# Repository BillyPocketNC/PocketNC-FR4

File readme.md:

# Support for this Project has been discontinued
This is an open source project and is not commercially supported.

For more information and files see [our Wiki](https://pocketnc.atlassian.net/wiki/spaces/PNFUR/pages/368902363/FR4+Resources) for more information

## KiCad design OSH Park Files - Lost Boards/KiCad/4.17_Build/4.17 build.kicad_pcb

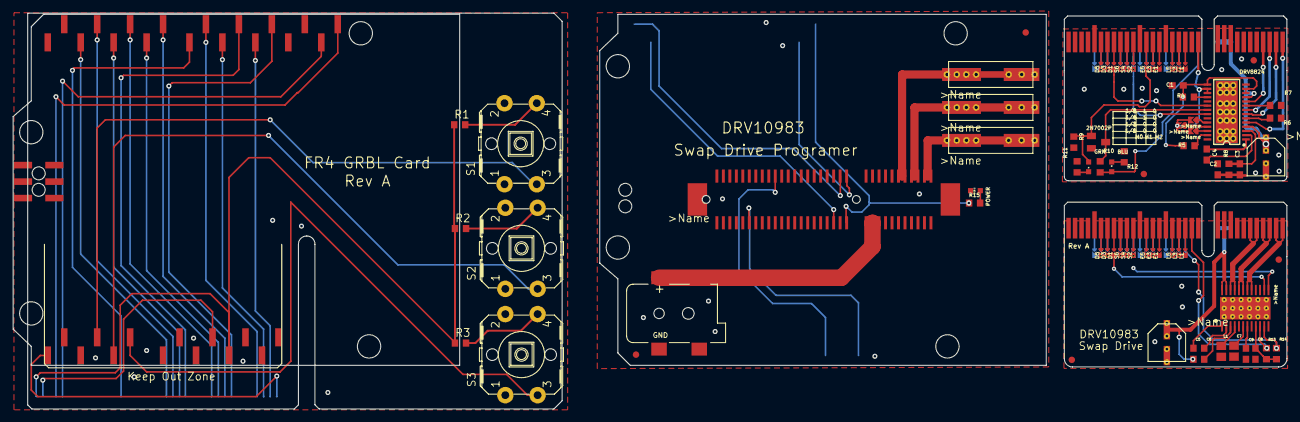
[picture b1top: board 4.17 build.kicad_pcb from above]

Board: 2 copper layers, 196.3 x 60.9 mm, 56 parts (0 on the bottom side), 77 nets.

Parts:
2N7002P: SOT23
BLACK: 104188-0110
BLU: CHIPLED_0603
C1: 4.7uf; C0603
C2: .01uf; C0603
C3, C4, C5, C6: .1uf; C0603
C7: 10uf; C0805
C8, C9: 1uf; C0603
CN1: DCJACK_2MM_SMT
DRV8824: DRV8824; HTSSOP-28
GRN: CHIPLED_0603
L1: 47uh; C0805
M0, M2, M3: SELECTIVE_CONNECT
M1, M4: ARDUINO_R3_ICSPSMT; ARDUINOR3_ICSP_SMT
POWER: CHIP-LED0603
R1, R2, R3, R10, R13, R14: 5k; R0603
R4, R5, R9: 10k; R0603
R6, R7: R0603
R8: 1m; R0603
R11, R12, R15: 460; R0603
RED: 104188-0110
S1, S2, S3: B3F-40XX-ROUND
U$1: FR4_CARD_EDGE
U$2, U$7: PCIE_64_SMART_BOARD
U$3: STEP_DIAGRAM
U$4: EEEFK0J220R
U$5, U$6, U$10, U$11, U$13, U$14: FIDUCIAL; FIDUCIAL_1MM
U$8: DRV10983; HTSS0P-24
U$9: 10uf; EEEFK0J220R
U$12: 10061913-101CLF; 10076266-100CLF
YELLOW: 104188-0110

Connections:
3.3V: C1.1, DRV8824.12, DRV8824.13, DRV8824.15, R4.2, R5.2
3V: M1.3V, R1.1, R2.1, R3.1, U$1.P$1
3V1: BLU.A, R10.2, U$2.P$12
3V2: M4.3V, R15.1, U$12.P$12
5V: M1.5V, U$1.P$2
5V1: DRV8824.16, DRV8824.17, M0.P$2, M2.P$2, M3.P$2, U$2.P$44
5V2: M4.5V, U$12.P$44
A1: DRV8824.5, U$2.P$33
A2: DRV8824.7, U$2.P$34
B1: DRV8824.10, U$2.P$36
B2: DRV8824.8, U$2.P$35
DIR: DRV8824.20, U$2.P$57@1
DIR1: U$7.P$57@1, U$8.P$14
DIR2: M4.D13, U$12.P$27
DIR_X: M1.D5, U$1.P$28
DIR_Y: M1.D6, U$1.P$29
DIR_Z: M1.D7, U$1.P$30
ENBL: M1.D8, U$1.P$14
ENBL-IN: 2N7002P.1, GRN.A, R9.2, U$2.P$50@1
ENBL-OUT: 2N7002P.3, DRV8824.21, R10.1
FEED_HOLD: M1.A1, S2.3
GND: M1.GND, M1.GND@1, M1.GND@2, S1.1, S2.1, S3.1, U$1.P$3, U$1.P$12, U$1.P$20, U$1.P$27, U$1.P$34
GND1: 2N7002P.2, C1.2, C4.2, DRV8824.14, DRV8824.28, DRV8824.GND@10, DRV8824.GND@11, DRV8824.GND@12, DRV8824.GND@13, DRV8824.GND@14, DRV8824.GND@15, DRV8824.GND@16, DRV8824.GND@17, DRV8824.GND@18, DRV8824.GND@19, DRV8824.GND@20, DRV8824.GND@21, DRV8824.GND@22, DRV8824.GND@23, DRV8824.GND@24, DRV8824.GND@25, DRV8824.GND@26, DRV8824.GND@27, DRV8824.GND@28, DRV8824.GND@29, DRV8824.GND@30, DRV8824.GND@PAD, R6.1, R7.1, R9.1, R11.2, R12.2, U$2.GND@1, U$2.GND@2, U$2.GND@3, U$2.P$13, U$2.P$25, U$2.P$49, U$2.P$53, U$2.P$60, U$4.P$2
GND2: C7.1, C8.1, C9.1, L1.2, U$7.GND@1, U$7.GND@2, U$7.GND@3, U$7.P$13, U$7.P$25, U$7.P$49, U$7.P$53, U$7.P$60, U$8.GND, U$8.GND@1, U$8.GND@3, U$8.GND@4, U$8.GND@5, U$8.GND@6, U$8.GND@7, U$8.GND@8, U$8.GND@9, U$8.GND@10, U$8.GND@11, U$8.GND@12, U$8.GND@13, U$8.GND@14, U$8.GND@15, U$8.GND@16, U$8.GND@17, U$8.GND@18, U$8.GND@19, U$8.GND@20, U$8.P$5, U$8.P$8, U$8.P$15, U$8.P$16, U$9.P$2
GND3: CN1.GND, CN1.GNDBREAK, M4.GND, M4.GND@1, M4.GND@2, POWER.C, U$12.P$13, U$12.P$25, U$12.P$41, U$12.P$42, U$12.P$43, U$12.P$49, U$12.P$53, U$12.P$60
LIM_X: M1.D9, U$1.P$35
LIM_Y: M1.D10, U$1.P$36
LIM_Z: M1.D12, U$1.P$37
unnamed: C2.2, DRV8824.1
unnamed: R1.2, S1.4
unnamed: C2.1, DRV8824.2
unnamed: DRV8824.9, R7.2
unnamed: R2.2, S2.4
unnamed: DRV8824.6, R6.2
unnamed: DRV8824.18, R4.1
unnamed: R3.2, S3.4
unnamed: BLU.C, R12.1
unnamed: GRN.C, R11.1
unnamed: C5.2, U$8.P$1
unnamed: C6.2, U$8.P$2
unnamed: C6.1, U$8.P$3
unnamed: C7.2, U$8.P$6
unnamed: L1.1, U$8.P$4
unnamed: DRV8824.27, R5.1
unnamed: DRV8824.26, M2.P$1
unnamed: DRV8824.25, M3.P$1
unnamed: DRV8824.24, M0.P$1
unnamed: C9.2, U$8.P$7
unnamed: POWER.A, R15.2
PROBE: M1.A5, U$1.P$38
PWM: U$7.P$22@1, U$8.P$13
PWM1: M4.D11, U$12.P$55
RESET/ABORT: M1.A0, S3.3
SCL: M1.SCL, U$1.P$4
SCL1: R13.2, U$7.P$45, U$8.P$10
SCL2: M4.A5, U$12.P$45
SDA: M1.SDA, U$1.P$5
SDA1: R14.2, U$7.P$14, U$8.P$11
SDA2: M4.A4, U$12.P$14
SP_DIR: M1.D13, U$1.P$31
SP_PWM: M1.D11, U$1.P$24
START/RESUME: M1.A2, S1.3
STEP: DRV8824.22, U$2.P$22@1
STEP_X: M1.D2, U$1.P$21
STEP_Y: M1.D3, U$1.P$22
STEP_Z: M1.D4, U$1.P$23
U: U$7.P$33, U$7.P$34, U$8.P$17, U$8.P$18
U1: U$12.P$33, U$12.P$34, YELLOW.1@1
V: U$7.P$35, U$7.P$36, U$8.P$19, U$8.P$20
V1: RED.1@1, U$12.P$35, U$12.P$36
V3P3: C8.2, R13.1, R14.1, U$8.P$9
VCC: C3.1, C4.1, DRV8824.4, DRV8824.11, R8.1, U$2.P$9, U$2.P$10, U$2.P$11, U$4.P$1
VCC1: C5.1, U$7.P$9, U$7.P$10, U$7.P$11, U$8.P$23, U$8.P$24, U$9.P$1
VCC2: CN1.PWR1, U$12.P$9, U$12.P$10, U$12.P$11
VCP: C3.2, DRV8824.3, R8.2
W: U$7.P$37, U$7.P$38, U$8.P$21, U$8.P$22
W1: BLACK.1@1, U$12.P$37, U$12.P$38

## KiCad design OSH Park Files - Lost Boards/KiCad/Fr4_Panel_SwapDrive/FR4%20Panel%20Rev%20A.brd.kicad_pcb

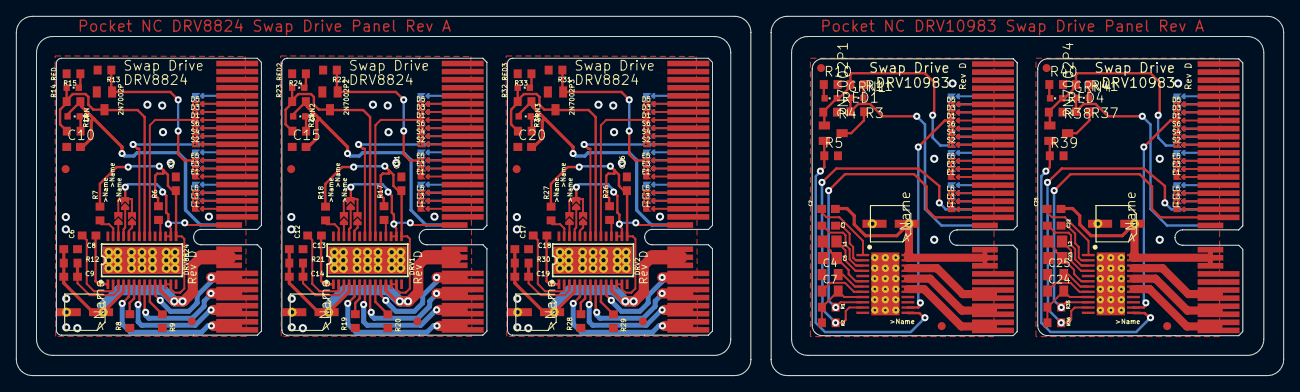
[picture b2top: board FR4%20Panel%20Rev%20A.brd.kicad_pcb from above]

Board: 2 copper layers, 157.0 x 44.5 mm, 117 parts (0 on the bottom side), 117 nets.

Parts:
2N7002P, 2N7002P1, 2N7002P2, 2N7002P3, 2N7002P4: SOT23
C1, C11, C16: 4.7uf; C0603
C2, C3, C8, C9, C10, C13, C14, C15, C18, C19, C20, C21, C22: .1uf; C0603
C4, C7, C24, C25: C0805K
C5, C23: 10uf; C0805
C6, C12, C17: .01uf; C0603
DRV1, DRV2, DRV8824: DRV8824; HTSSOP-28
GRN, GRN1, GRN2, GRN3, GRN4: CHIPLED_0603
L1, L2: 47uh; C0805
M0, M1, M2, M3, M4, M5, M6, M7, M8: SELECTIVE_CONNECT
R1, R2, R35, R36: 5k; R0603
R3, R10, R11, R14, R15, R16, R23, R24, R25, R32, R33, R34, R37, R40, R41: 460; R0603
R4, R5, R6, R7, R13, R17, R18, R22, R26, R27, R31, R38, R39: 10k; R0603
R8, R9, R19, R20, R28, R29: R0603
R12, R21, R30: 1m; R0603
RED, RED1, RED2, RED3, RED4: CHIPLED_0603
U$1, U$6, U$10, U$14, U$18: PCIE_64_SMART_BOARD
U$2, U$19: DRV10983; HTSS0P-24
U$3, U$20: 10uf; EEEFK0J220R
U$4, U$5, U$8, U$9, U$12, U$13, U$16, U$17, U$21, U$22: FIDUCIAL; FIDUCIAL_1MM
U$7, U$11, U$15: EEEFK0J220R

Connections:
3.3V: C1.1, DRV8824.12, DRV8824.13, DRV8824.15, R6.2, R7.2
3.3V1: C11.1, DRV1.12, DRV1.13, DRV1.15, R17.2, R18.2
3.3V2: C16.1, DRV2.12, DRV2.13, DRV2.15, R26.2, R27.2
3V: GRN1.A, R3.2, U$1.P$12
3V1: C10.2, GRN.A, R14.2, U$6.P$12
3V2: C15.2, GRN2.A, R23.2, U$10.P$12
3V3: C20.2, GRN3.A, R32.2, U$14.P$12
3V4: GRN4.A, R37.2, U$18.P$12
5V: DRV8824.16, DRV8824.17, M0.P$2, M1.P$2, M2.P$2, U$6.P$44
5V1: DRV1.16, DRV1.17, M3.P$2, M4.P$2, M5.P$2, U$10.P$44
5V2: DRV2.16, DRV2.17, M6.P$2, M7.P$2, M8.P$2, U$14.P$44
A1: DRV8824.5, U$6.P$33, U$6.P$34
A2: DRV8824.7, U$6.P$35, U$6.P$36
A3: DRV1.5, U$10.P$33, U$10.P$34
A4: DRV1.7, U$10.P$35, U$10.P$36
A5: DRV2.5, U$14.P$33, U$14.P$34
A6: DRV2.7, U$14.P$35, U$14.P$36
B1: DRV8824.10, U$6.P$39, U$6.P$40
B2: DRV8824.8, U$6.P$37, U$6.P$38
B3: DRV1.8, U$10.P$37, U$10.P$38
B4: DRV1.10, U$10.P$39, U$10.P$40
B5: DRV2.8, U$14.P$37, U$14.P$38
B6: DRV2.10, U$14.P$39, U$14.P$40
DIR: U$1.P$57@1, U$2.P$14
DIR1: DRV8824.20, U$6.P$57@1
DIR2: DRV1.20, U$10.P$57@1
DIR3: DRV2.20, U$14.P$57@1
DIR4: U$18.P$57@1, U$19.P$14
ENBL: 2N7002P1.1, R4.2, R11.2, RED1.A, U$1.P$22@1
ENBL1: 2N7002P4.1, R38.2, R41.2, RED4.A, U$18.P$22@1
ENBL-IN: 2N7002P.1, R13.2, U$6.P$50@1
ENBL-IN1: 2N7002P2.1, R22.2, U$10.P$50@1
ENBL-IN2: 2N7002P3.1, R31.2, U$14.P$50@1
ENBL-OUT: 2N7002P.3, DRV8824.21, R14.1, R16.2, RED.A
ENBL-OUT1: 2N7002P2.3, DRV1.21, R23.1, R25.2, RED2.A
ENBL-OUT2: 2N7002P3.3, DRV2.21, R32.1, R34.2, RED3.A
GND: C4.1, C5.1, C7.1, R4.1, R5.2, R10.2, U$1.GND@1, U$1.GND@2, U$1.GND@3, U$1.P$13, U$1.P$25, U$1.P$49, U$1.P$53, U$1.P$60, U$2.GND, U$2.GND@1, U$2.GND@3, U$2.GND@4, U$2.GND@5, U$2.GND@6, U$2.GND@7, U$2.GND@8, U$2.GND@9, U$2.GND@10, U$2.GND@11, U$2.GND@12, U$2.GND@13, U$2.GND@14, U$2.GND@15, U$2.GND@16, U$2.GND@17, U$2.GND@18, U$2.GND@19, U$2.GND@20, U$2.P$5, U$2.P$8, U$2.P$15, U$2.P$16, U$3.GND@2
GND1: 2N7002P.2, C1.2, C8.2, C10.1, DRV8824.14, DRV8824.28, DRV8824.GND@10, DRV8824.GND@11, DRV8824.GND@12, DRV8824.GND@13, DRV8824.GND@14, DRV8824.GND@15, DRV8824.GND@16, DRV8824.GND@17, DRV8824.GND@18, DRV8824.GND@19, DRV8824.GND@20, DRV8824.GND@21, DRV8824.GND@22, DRV8824.GND@23, DRV8824.GND@24, DRV8824.GND@25, DRV8824.GND@26, DRV8824.GND@27, DRV8824.GND@28, DRV8824.GND@29, DRV8824.GND@30, DRV8824.GND@PAD, R8.1, R9.1, R13.1, R15.2, U$6.GND@1, U$6.GND@2, U$6.GND@3, U$6.P$13, U$6.P$25, U$6.P$49, U$6.P$53, U$6.P$60, U$7.GND@2
GND2: 2N7002P2.2, C11.2, C13.2, C15.1, DRV1.14, DRV1.28, DRV1.GND@10, DRV1.GND@11, DRV1.GND@12, DRV1.GND@13, DRV1.GND@14, DRV1.GND@15, DRV1.GND@16, DRV1.GND@17, DRV1.GND@18, DRV1.GND@19, DRV1.GND@20, DRV1.GND@21, DRV1.GND@22, DRV1.GND@23, DRV1.GND@24, DRV1.GND@25, DRV1.GND@26, DRV1.GND@27, DRV1.GND@28, DRV1.GND@29, DRV1.GND@30, DRV1.GND@PAD, R19.1, R20.1, R22.1, R24.2, U$10.GND@1, U$10.GND@2, U$10.GND@3, U$10.P$13, U$10.P$25, U$10.P$49, U$10.P$53, U$10.P$60, U$11.GND@2
GND3: 2N7002P3.2, C16.2, C18.2, C20.1, DRV2.14, DRV2.28, DRV2.GND@10, DRV2.GND@11, DRV2.GND@12, DRV2.GND@13, DRV2.GND@14, DRV2.GND@15, DRV2.GND@16, DRV2.GND@17, DRV2.GND@18, DRV2.GND@19, DRV2.GND@20, DRV2.GND@21, DRV2.GND@22, DRV2.GND@23, DRV2.GND@24, DRV2.GND@25, DRV2.GND@26, DRV2.GND@27, DRV2.GND@28, DRV2.GND@29, DRV2.GND@30, DRV2.GND@PAD, R28.1, R29.1, R31.1, R33.2, U$14.GND@1, U$14.GND@2, U$14.GND@3, U$14.P$13, U$14.P$25, U$14.P$49, U$14.P$53, U$14.P$60, U$15.GND@2
GND4: C23.1, C24.1, C25.1, R38.1, R39.2, R40.2, U$18.GND@1, U$18.GND@2, U$18.GND@3, U$18.P$13, U$18.P$25, U$18.P$49, U$18.P$53, U$18.P$60, U$19.GND, U$19.GND@1, U$19.GND@3, U$19.GND@4, U$19.GND@5, U$19.GND@6, U$19.GND@7, U$19.GND@8, U$19.GND@9, U$19.GND@10, U$19.GND@11, U$19.GND@12, U$19.GND@13, U$19.GND@14, U$19.GND@15, U$19.GND@16, U$19.GND@17, U$19.GND@18, U$19.GND@19, U$19.GND@20, U$19.P$5, U$19.P$8, U$19.P$15, U$19.P$16, U$20.GND@2
unnamed: C2.2, U$2.P$1
unnamed: C3.2, U$2.P$2
unnamed: C3.1, U$2.P$3
unnamed: DRV8824.6, R8.2
unnamed: R10.1, RED1.C
unnamed: C4.2, U$2.P$7
unnamed: C6.2, DRV8824.1
unnamed: GRN1.C, R11.1
unnamed: 2N7002P1.3, R3.1
unnamed: C6.1, DRV8824.2
unnamed: DRV8824.9, R9.2
unnamed: DRV8824.18, R6.1
unnamed: GRN.C, R16.1
unnamed: R15.1, RED.C
unnamed: DRV1.6, R19.2
unnamed: DRV8824.27, R7.1
unnamed: DRV8824.26, M2.P$1
unnamed: DRV8824.25, M1.P$1
unnamed: DRV8824.24, M0.P$1
unnamed: DRV1.27, R18.1
unnamed: DRV1.26, M3.P$1
unnamed: DRV1.25, M4.P$1
unnamed: DRV1.24, M5.P$1
unnamed: C12.2, DRV1.1
unnamed: C12.1, DRV1.2
unnamed: DRV1.9, R20.2
unnamed: DRV1.18, R17.1
unnamed: GRN2.C, R25.1
unnamed: R24.1, RED2.C
unnamed: DRV2.6, R28.2
unnamed: DRV2.27, R27.1
unnamed: DRV2.26, M6.P$1
unnamed: DRV2.25, M7.P$1
unnamed: DRV2.24, M8.P$1
unnamed: C17.2, DRV2.1
unnamed: C17.1, DRV2.2
unnamed: DRV2.9, R29.2
unnamed: DRV2.18, R26.1
unnamed: GRN3.C, R34.1
unnamed: R33.1, RED3.C
unnamed: C21.2, U$19.P$1
unnamed: C22.2, U$19.P$2
unnamed: C22.1, U$19.P$3
unnamed: C25.2, U$19.P$7
unnamed: 2N7002P4.3, R37.1
unnamed: R40.1, RED4.C
unnamed: GRN4.C, R41.1
PWM: 2N7002P1.2, R5.1, U$2.P$13
PWM1: 2N7002P4.2, R39.1, U$19.P$13
SCL: R1.2, U$1.P$45, U$2.P$10
SCL1: R35.2, U$18.P$45, U$19.P$10
SDA: R2.2, U$1.P$14, U$2.P$11
SDA1: R36.2, U$18.P$14, U$19.P$11
STEP: DRV8824.22, U$6.P$22@1
STEP1: DRV1.22, U$10.P$22@1
STEP2: DRV2.22, U$14.P$22@1
SW: L1.2, U$2.P$4
SW1: L2.2, U$19.P$4
U: U$1.P$33, U$1.P$34, U$2.P$17, U$2.P$18
U1: U$18.P$33, U$18.P$34, U$19.P$17, U$19.P$18
V: U$1.P$35, U$1.P$36, U$2.P$19, U$2.P$20
V1: U$18.P$35, U$18.P$36, U$19.P$19, U$19.P$20
V3P1: C24.2, R35.1, R36.1, U$19.P$9
V3P3: C7.2, R1.1, R2.1, U$2.P$9
VCC: C2.1, U$1.VCC@1, U$1.VCC@2, U$1.VCC@3, U$2.P$23, U$2.P$24, U$3.P$3
VCC1: C8.1, C9.1, DRV8824.4, DRV8824.11, R12.1, U$6.VCC@1, U$6.VCC@2, U$6.VCC@3, U$7.P$3
VCC2: C13.1, C14.1, DRV1.4, DRV1.11, R21.1, U$10.VCC@1, U$10.VCC@2, U$10.VCC@3, U$11.P$3
VCC3: C18.1, C19.1, DRV2.4, DRV2.11, R30.1, U$14.VCC@1, U$14.VCC@2, U$14.VCC@3, U$15.P$3
VCC4: C21.1, U$18.VCC@1, U$18.VCC@2, U$18.VCC@3, U$19.P$23, U$19.P$24, U$20.P$3
VCP: C9.2, DRV8824.3, R12.2
VCP1: C14.2, DRV1.3, R21.2
VCP2: C19.2, DRV2.3, R30.2
VREG: C5.2, L1.1, U$2.P$6
VREG1: C23.2, L2.1, U$19.P$6
W: U$1.P$37, U$1.P$38, U$2.P$21, U$2.P$22
W1: U$18.P$37, U$18.P$38, U$19.P$21, U$19.P$22

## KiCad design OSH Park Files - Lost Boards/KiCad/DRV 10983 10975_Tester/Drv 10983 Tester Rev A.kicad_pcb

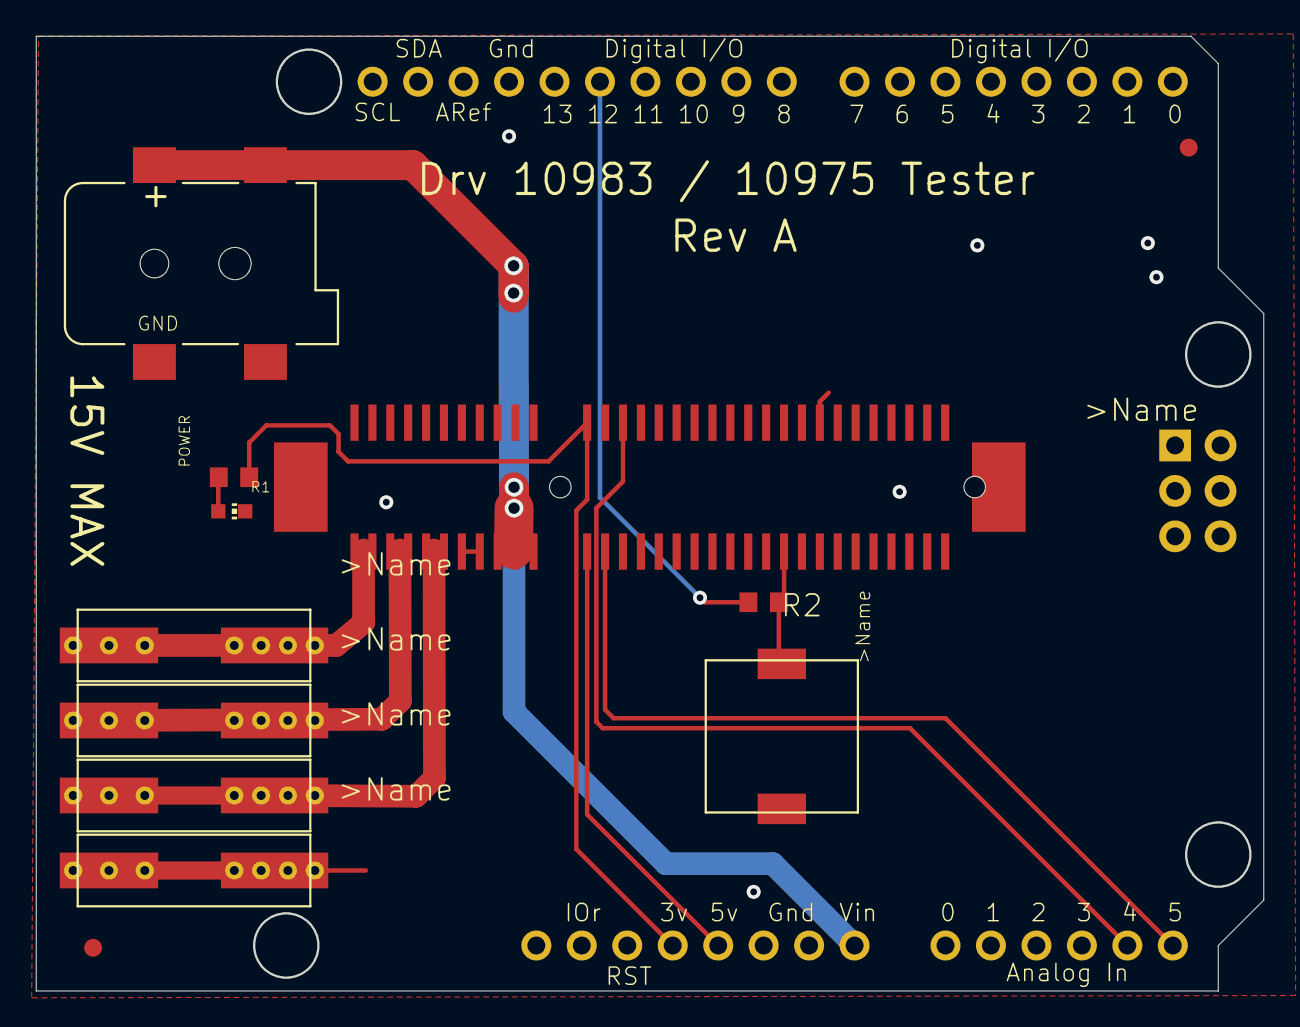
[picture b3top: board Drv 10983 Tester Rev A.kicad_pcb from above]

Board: 2 copper layers, 68.5 x 53.3 mm, 13 parts (0 on the bottom side), 13 nets.

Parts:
BLACK: 104188-0110
CN1: DCJACK_2MM_SMT
GND: 104188-0110
M2: ARDUINO_R3_ICSP; ARDUINOR3_ICSP
POWER: CHIP-LED0603
R1: 460; R0603
R2: 220; R0603
RED: 104188-0110
U$1: 10061913-101CLF; 10076266-100CLF
U$2, U$3: FIDUCIAL; FIDUCIAL_1MM
U$4: BUTTON_SKSTAAE010
YELLOW: 104188-0110

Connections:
3V: M2.3V, R1.1, U$1.P$12
5V: M2.5V, U$1.P$44
ENBL: R2.1, U$1.P$55, U$4.P$1
GND: CN1.GND, CN1.GNDBREAK, GND.1@1, M2.GND, M2.GND@1, M2.GND@3, POWER.C, U$1.P$9, U$1.P$10, U$1.P$11, U$1.P$13, U$1.P$25, U$1.P$49, U$1.P$53, U$1.P$60, U$4.P$2
unnamed: POWER.A, R1.2
unnamed: M2.D12, R2.2
O: U$1.P$39, U$1.P$40
SCL: M2.A5, U$1.P$45
SDA: M2.A4, U$1.P$14
U: U$1.P$33, U$1.P$34, YELLOW.1@1
V: RED.1@1, U$1.P$35, U$1.P$36
VCC: CN1.PWR1, M2.VIN, U$1.P$41, U$1.P$42, U$1.P$43
W: BLACK.1@1, U$1.P$37, U$1.P$38

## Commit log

2020-03-31 Kicad Files
2020-03-31 All Fr4 docs + KiCad Conversion
2020-07-23 added missing driver files from OSH Park
2021-06-23 Converted a few of the swapp drive boards to KiCad
